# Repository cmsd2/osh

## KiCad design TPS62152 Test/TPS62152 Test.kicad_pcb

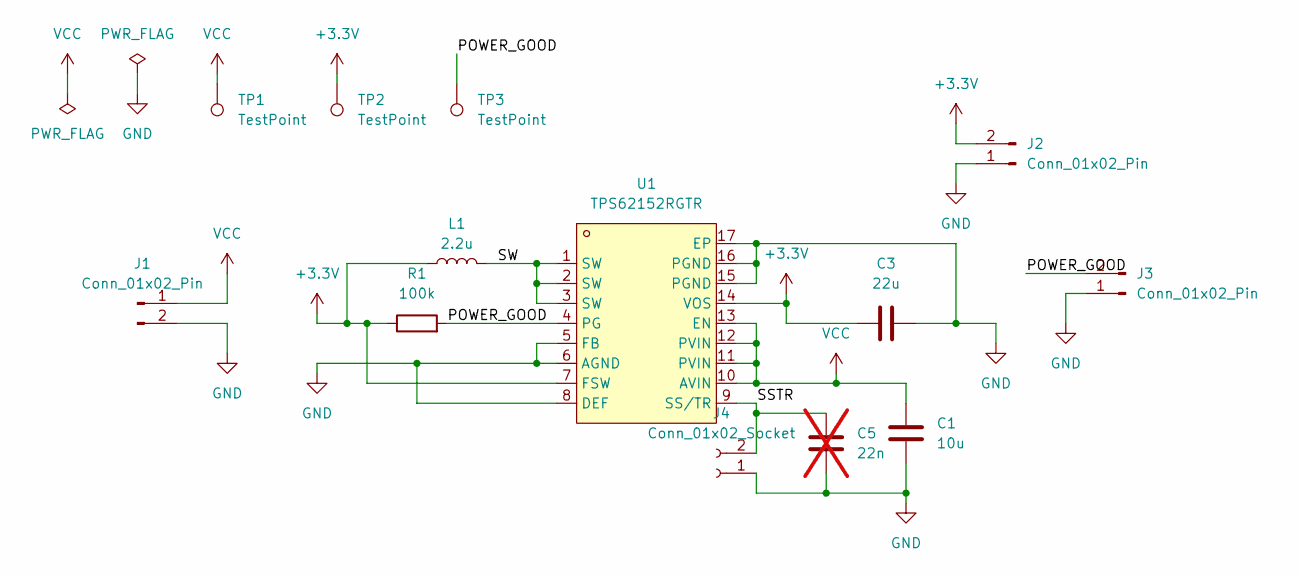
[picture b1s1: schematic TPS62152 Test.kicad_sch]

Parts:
C1: 10u; C0805; LCSC C440198
C3: 22u; C0805; LCSC C440198
C5: 22n; C0603; LCSC C21122; not fitted
J1, J2, J3: Conn_01x02_Pin; HDR-TH_2P-P2.54-V-M
J4: Conn_01x02_Socket; PinSocket_1x02_P2.54mm_Vertical; LCSC C3322502
L1: 2.2u; IND-SMD_L2.5-W2.0-B; LCSC C22471111
R1: 100k; R0603; LCSC C14675
TP1, TP2, TP3: TestPoint; TestPoint_THTPad_1.0x1.0mm_Drill0.5mm
U1: TPS62152RGTR; TQFN-16_L3.0-W3.0-P0.50-TL-EP1.7; LCSC Part C2070611

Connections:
+3.3V: C3.1, J2.2, L1.1, R1.1, TP2.1, U1.7 (FSW), U1.14 (VOS)
/POWER_GOOD: J3.2, R1.2, TP3.1, U1.4 (PG)
/SSTR: C5.1, J4.2, U1.9 (SS/TR)
/SW: L1.2, U1.1 (SW), U1.2 (SW), U1.3 (SW)
GND: C1.2, C3.2, C5.2, J1.2, J2.1, J3.1, J4.1, U1.5 (FB), U1.6 (AGND), U1.8 (DEF), U1.15 (PGND), U1.16 (PGND), U1.17 (EP)
VCC: C1.1, J1.1, TP1.1, U1.10 (AVIN), U1.11 (PVIN), U1.12 (PVIN), U1.13 (EN)

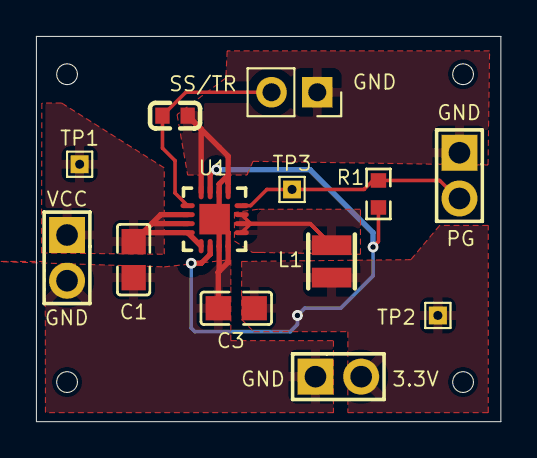
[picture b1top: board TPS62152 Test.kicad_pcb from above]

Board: 2 copper layers, 25.8 x 21.4 mm, 13 parts (0 on the bottom side), 6 nets.

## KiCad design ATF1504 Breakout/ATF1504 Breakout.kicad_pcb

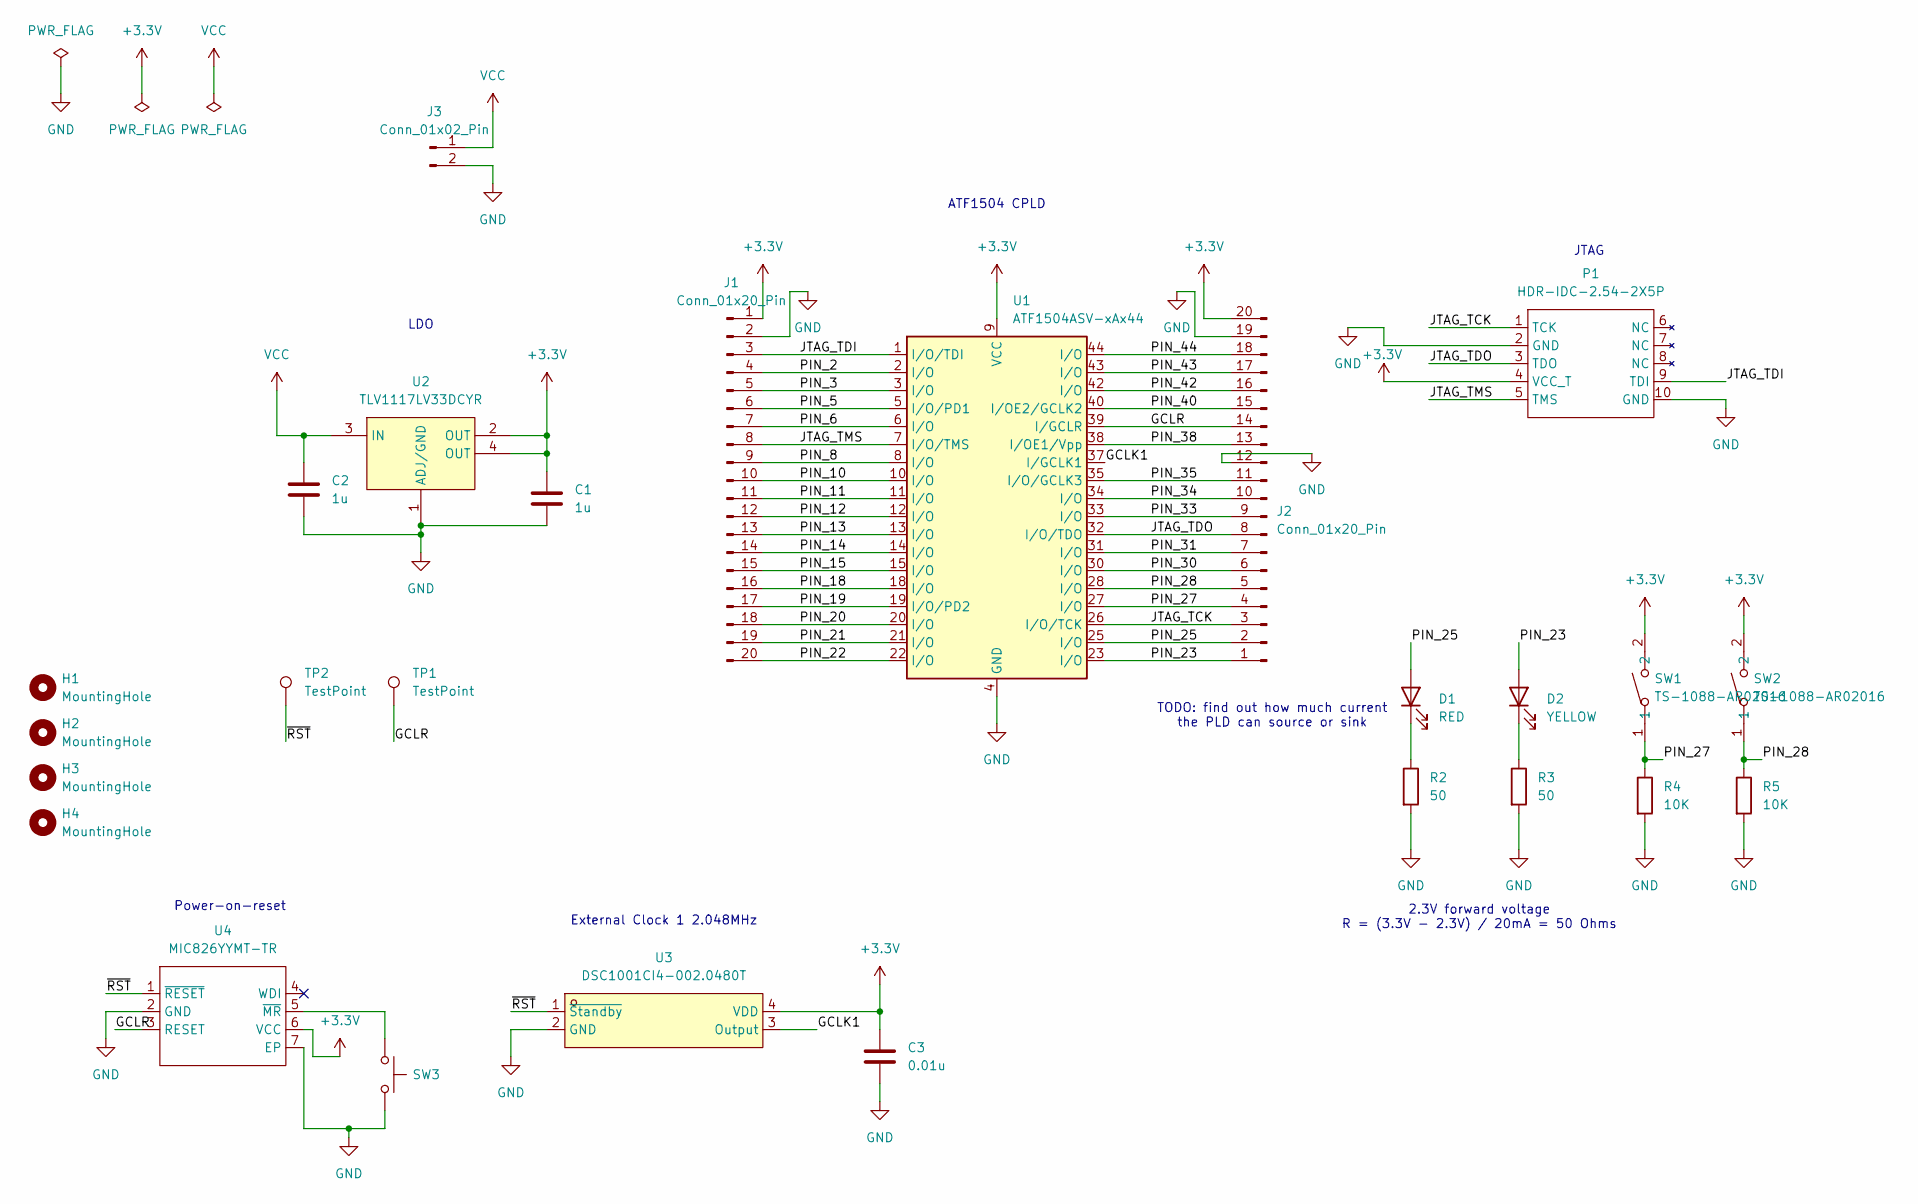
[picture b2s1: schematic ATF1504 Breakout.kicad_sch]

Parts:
C1, C2: 1u; C0603; LCSC C48579283
C3: 0.01u; C0603; LCSC C327204
D1: RED; LED0603-RD_RED; LCSC C965799
D2: YELLOW; LED0603-RD-YELLOW; LCSC C965803
H1, H2, H3, H4: MountingHole; MountingHole_3mm
J1, J2: Conn_01x20_Pin; HDR-TH_20P-P2.54-V-M-4; LCSC C7501591
J3: Conn_01x02_Pin; HDR-TH_2P-P2.54-V-M; LCSC C492401
P1: HDR-IDC-2.54-2X5P; IDC-TH_10P-P2.54_C5665; LCSC C5665
R2, R3: 50; R0603; LCSC C849792
R4, R5: 10K; R0603
SW1, SW2, SW3: TS-1088-AR02016; SW-SMD_L3.9-W3.0-P4.45; LCSC Part C720477
TP1, TP2: TestPoint; TestPoint_THTPad_1.0x1.0mm_Drill0.5mm
U1: ATF1504ASV-xAx44; TQFP-44_10x10mm_P0.8mm
U2: TLV1117LV33DCYR; SOT-223_L6.7-W3.5-P2.30-BR; LCSC Part C15578
U3: DSC1001CI4-002.0480T; OSC-SMD_4P-L3.2-W2.5-BL_1C210000BB0F; LCSC Part C611680
U4: MIC826YYMT-TR; TDFN-6_L2.0-W2.0-P0.65-TL-EP; LCSC Part C622518

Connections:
+3.3V: C1.1, C3.1, J1.1, J2.20, P1.4 (VCC_T), SW1.2, SW2.2, U1.9 (VCC), U1.17 (VCC), U1.29 (VCC), U1.41 (VCC), U2.2 (OUT), U2.4 (OUT), U3.4 (VDD), U4.6 (VCC)
/GCLK1: U1.37 (I/GCLK1), U3.3 (Output)
/GCLR: J2.14, TP1.1, U1.39 (I/GCLR), U4.3 (RESET)
/JTAG_TCK: J2.3, P1.1 (TCK), U1.26 (I/O/TCK)
/JTAG_TDI: J1.3, P1.9 (TDI), U1.1 (I/O/TDI)
/JTAG_TDO: J2.8, P1.3 (TDO), U1.32 (I/O/TDO)
/JTAG_TMS: J1.8, P1.5 (TMS), U1.7 (I/O/TMS)
/PIN_2: J1.4, U1.2 (I/O)
/PIN_3: J1.5, U1.3 (I/O)
/PIN_5: J1.6, U1.5 (I/O/PD1)
/PIN_6: J1.7, U1.6 (I/O)
/PIN_8: J1.9, U1.8 (I/O)
/PIN_10: J1.10, U1.10 (I/O)
/PIN_11: J1.11, U1.11 (I/O)
/PIN_12: J1.12, U1.12 (I/O)
/PIN_13: J1.13, U1.13 (I/O)
/PIN_14: J1.14, U1.14 (I/O)
/PIN_15: J1.15, U1.15 (I/O)
/PIN_18: J1.16, U1.18 (I/O)
/PIN_19: J1.17, U1.19 (I/O/PD2)
/PIN_20: J1.18, U1.20 (I/O)
/PIN_21: J1.19, U1.21 (I/O)
/PIN_22: J1.20, U1.22 (I/O)
/PIN_23: D2.2 (A), J2.1, U1.23 (I/O)
/PIN_25: D1.2 (A), J2.2, U1.25 (I/O)
/PIN_27: J2.4, R4.1, SW1.1, U1.27 (I/O)
/PIN_28: J2.5, R5.1, SW2.1, U1.28 (I/O)
/PIN_30: J2.6, U1.30 (I/O)
/PIN_31: J2.7, U1.31 (I/O)
/PIN_33: J2.9, U1.33 (I/O)
/PIN_34: J2.10, U1.34 (I/O)
/PIN_35: J2.11, U1.35 (I/O/GCLK3)
/PIN_38: J2.13, U1.38 (I/OE1/Vpp)
/PIN_40: J2.15, U1.40 (I/OE2/GCLK2)
/PIN_42: J2.16, U1.42 (I/O)
/PIN_43: J2.17, U1.43 (I/O)
/PIN_44: J2.18, U1.44 (I/O)
/~RST: TP2.1, U3.1 (~Standby), U4.1 (~RESET)
GND: C1.2, C2.2, C3.2, J1.2, J2.12, J2.19, J3.2, P1.2 (GND), P1.10 (GND), R2.2, R3.2, R4.2, R5.2, SW3.2, U1.4 (GND), U1.16 (GND), U1.24 (GND), U1.36 (GND), U2.1 (ADJ/GND), U3.2 (GND), U4.2 (GND), U4.7 (EP)
unnamed: D1.1 (K), R2.1
unnamed: D2.1 (K), R3.1
unnamed: SW3.1, U4.5 (~MR)
VCC: C2.1, J3.1, U2.3 (IN)

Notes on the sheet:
Power-on-reset
2.3V forward voltage R = (3.3V - 2.3V) / 20mA = 50 Ohms
ATF1504 CPLD
TODO: find out how much current the PLD can source or sink
External Clock 1 2.048MHz
JTAG
LDO

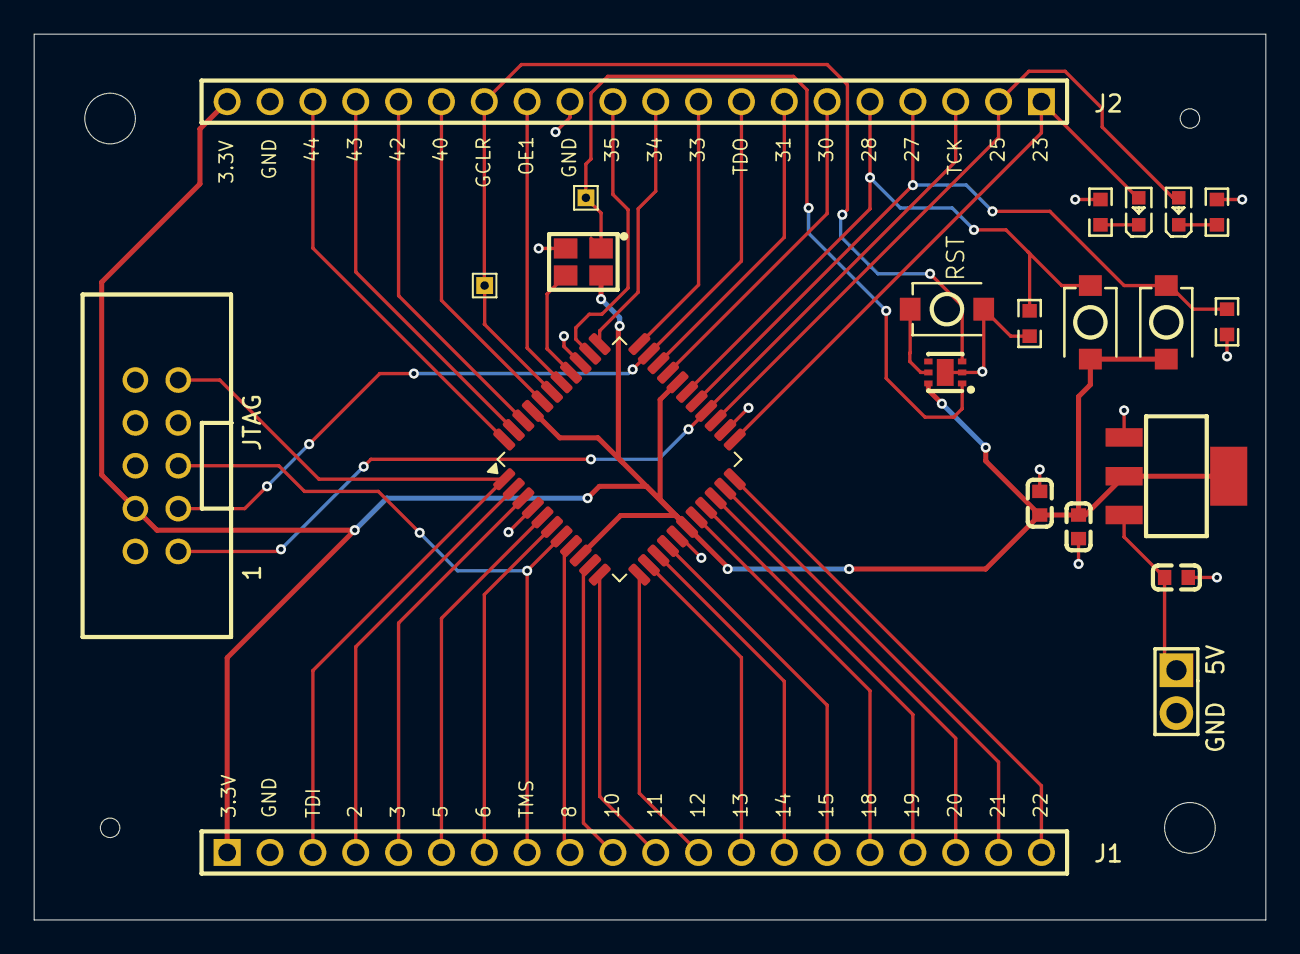
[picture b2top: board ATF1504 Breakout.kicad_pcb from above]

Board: 2 copper layers, 73.0 x 52.5 mm, 26 parts (0 on the bottom side), 43 nets.

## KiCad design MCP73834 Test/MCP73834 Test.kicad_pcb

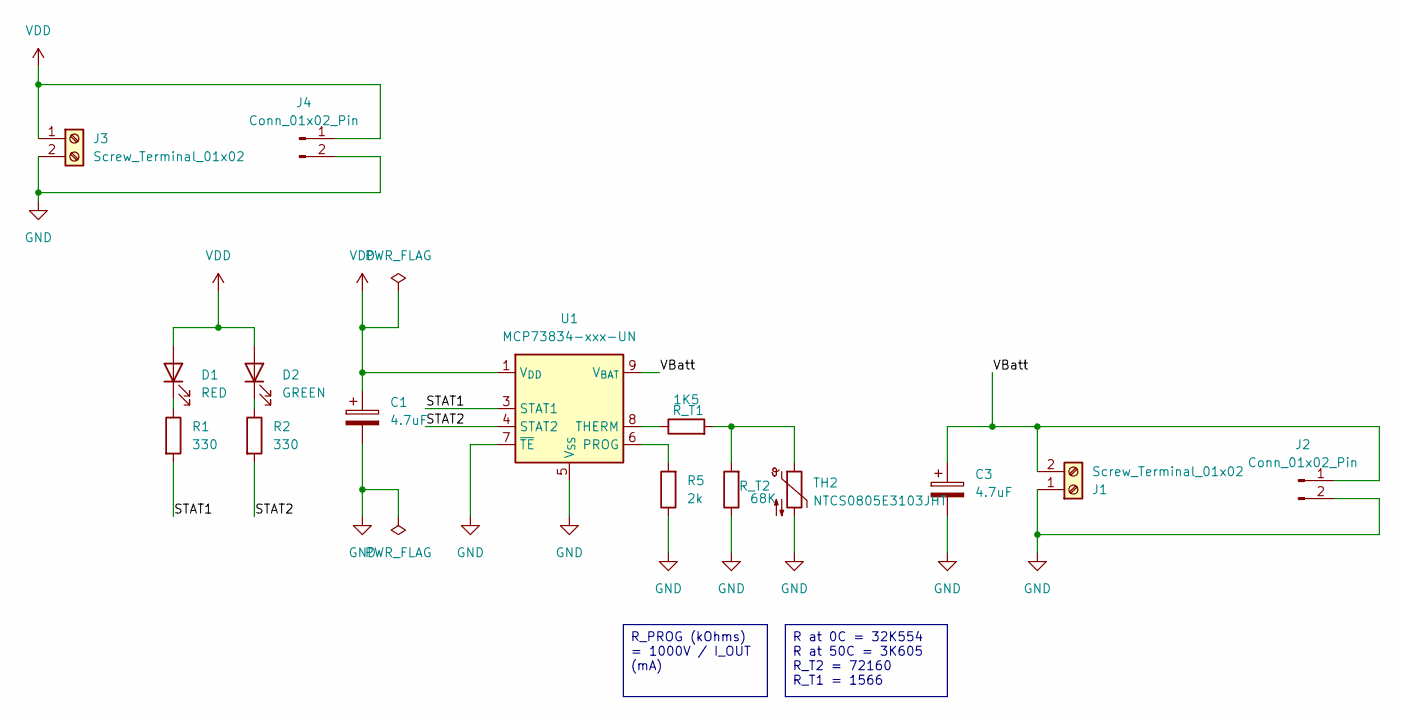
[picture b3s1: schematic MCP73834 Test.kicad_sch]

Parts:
C1, C3: 4.7uF; CAP-SMD_BD4.0-L4.3-W4.3-FD; LCSC C41435083
D1: RED; LED0805-RD_RED; LCSC C965812
D2: GREEN; LED0805-RD_GREEN; LCSC C965815
J1, J3: Screw_Terminal_01x02; CONN-TH_XY308-2.54-2P; LCSC C557685
J2, J4: Conn_01x02_Pin; HDR-TH_2P-P2.54-V-M; LCSC C7402729
R1, R2: 330; R0805; LCSC C105878
R3: 1K5; R0805; LCSC C114555
R4: 68K; R0805; LCSC C865614
R5: 2k; R0805; LCSC C114748
TH2: NTCS0805E3103JHT; R0805; LCSC C511025
U1: MCP73834-xxx-UN; MSOP-10_3x3mm_P0.5mm

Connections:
/STAT1: R1.2, U1.3 (STAT1)
/STAT2: R2.2, U1.4 (STAT2)
/VBatt: C3.1, J1.2, J2.1, U1.9 (V_{BAT}), U1.10 (V_{BAT})
GND: C1.2, C3.2, J1.1, J2.2, J3.2, J4.2, R4.1, R5.1, TH2.2, U1.5 (V_{SS}), U1.7 (~TE)
unnamed: D1.1 (K), R1.1
unnamed: D2.1 (K), R2.1
unnamed: R3.2, R4.2, TH2.1
unnamed: R5.2, U1.6 (PROG)
unnamed: R3.1, U1.8 (THERM)
VDD: C1.1, D1.2 (A), D2.2 (A), J3.1, J4.1, U1.1 (V_{DD}), U1.2 (V_{DD})

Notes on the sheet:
R_PROG (kOhms) = 1000V / I_OUT (mA)
R at 0C = 32K554 R at 50C = 3K605 R_T2 = 72160 R_T1 = 1566

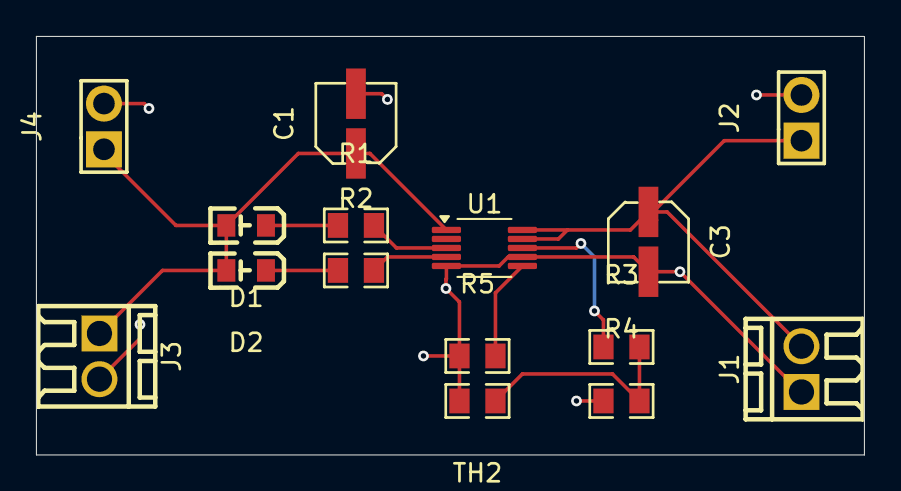
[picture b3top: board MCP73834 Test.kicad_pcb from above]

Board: 2 copper layers, 46.0 x 23.2 mm, 15 parts (0 on the bottom side), 10 nets.

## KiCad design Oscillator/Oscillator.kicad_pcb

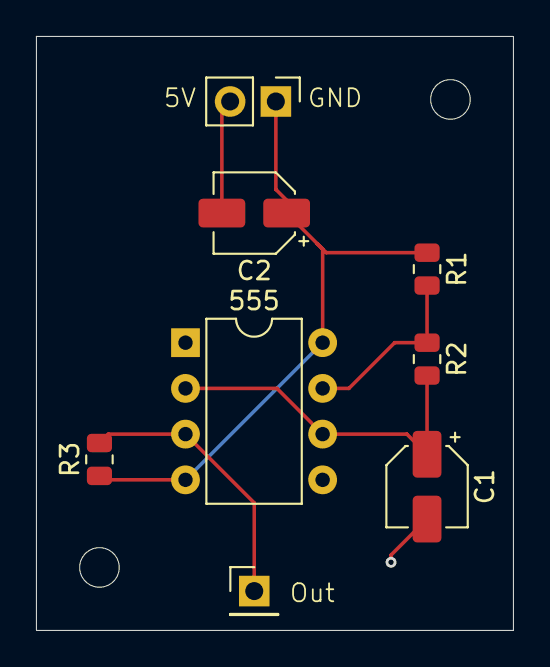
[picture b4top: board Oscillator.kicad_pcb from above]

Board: 2 copper layers, 26.5 x 33.0 mm, 8 parts (0 on the bottom side), 5 nets.

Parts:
555: NE555P; DIP-8_W7.62mm
C1, C2: C_Polarized; CP_Elec_4x5.4
J1: Conn_01x01_Pin; PinHeader_1x01_P2.54mm_Vertical
J2: Conn_01x02_Pin; PinHeader_1x02_P2.54mm_Vertical
R1, R2, R3: R; R_0805_2012Metric

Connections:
/Output: 555.3 (Q), J1.1, R3.2
/Trigger: 555.2 (TR), 555.6 (THR), C1.1, R2.2
GND: 555.1 (GND), C1.2, C2.2, J2.2
unnamed: 555.7 (DIS), R1.2, R2.1
VCC 5V: 555.4 (R), 555.8 (VCC), C2.1, J2.1, R1.1, R3.1

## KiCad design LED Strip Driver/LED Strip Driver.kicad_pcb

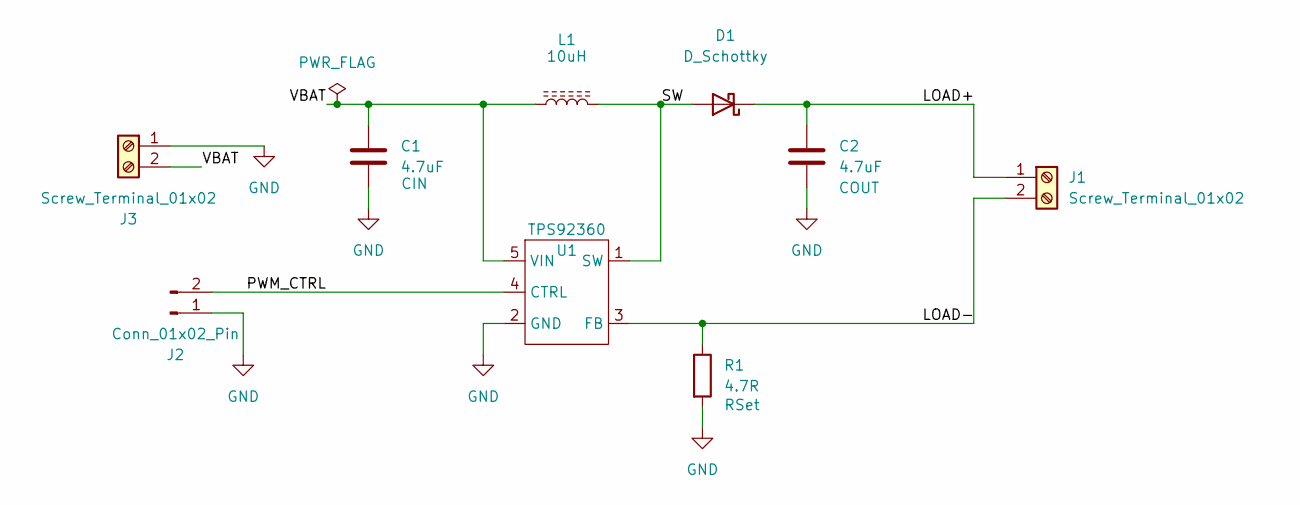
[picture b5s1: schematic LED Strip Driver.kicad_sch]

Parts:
C1, C2: 4.7uF; C_0805_2012Metric_Pad1.18x1.45mm_HandSolder; Part CL21A475KBQNNNE
D1: D_Schottky; D_SOD-323_HandSoldering; Part NSR0240HT1G
J1, J3: Screw_Terminal_01x02; TerminalBlock_Phoenix_PT-1,5-2-5.0-H_1x02_P5.00mm_Horizontal
J2: Conn_01x02_Pin; PinHeader_1x02_P2.54mm_Vertical
L1: 10uH; L_Coilcraft_LPS4018; Part LPS4018-103MRC
R1: 4.7R; R_0805_2012Metric_Pad1.20x1.40mm_HandSolder; Part CRCW08054R70FNEA
U1: TPS92360; SOT65P210X110-5N

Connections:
/LOAD+: C2.1, D1.1 (K), J1.1
/LOAD-: J1.2, R1.1, U1.3 (FB)
/PWM_CTRL: J2.2, U1.4 (CTRL)
/SW: D1.2 (A), L1.2, U1.1 (SW)
/VBAT: C1.1, J3.2, L1.1, U1.5 (VIN)
GND: C1.2, C2.2, J2.1, J3.1, R1.2, U1.2 (GND)

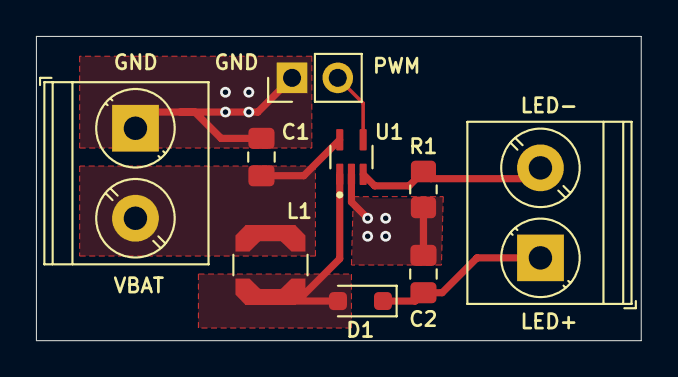
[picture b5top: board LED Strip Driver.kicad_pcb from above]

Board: 2 copper layers, 33.6 x 16.9 mm, 9 parts (0 on the bottom side), 6 nets.

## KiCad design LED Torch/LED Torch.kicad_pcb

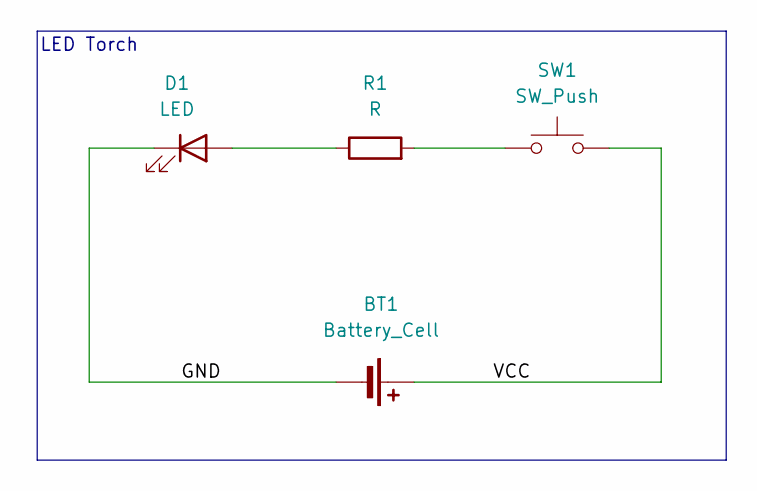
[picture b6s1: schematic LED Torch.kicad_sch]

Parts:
BT1: Battery_Cell; BatteryHolder_Keystone_1058_1x2032
D1: LED; LED_D5.0mm
R1: R; R_Axial_DIN0204_L3.6mm_D1.6mm_P7.62mm_Horizontal
SW1: SW_Push; SW_TH_Tactile_Omron_B3F-10xx

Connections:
/GND: BT1.2 (-), D1.1 (K)
/VCC: BT1.1 (+), SW1.2
unnamed: D1.2 (A), R1.1
unnamed: R1.2, SW1.1

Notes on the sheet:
LED Torch

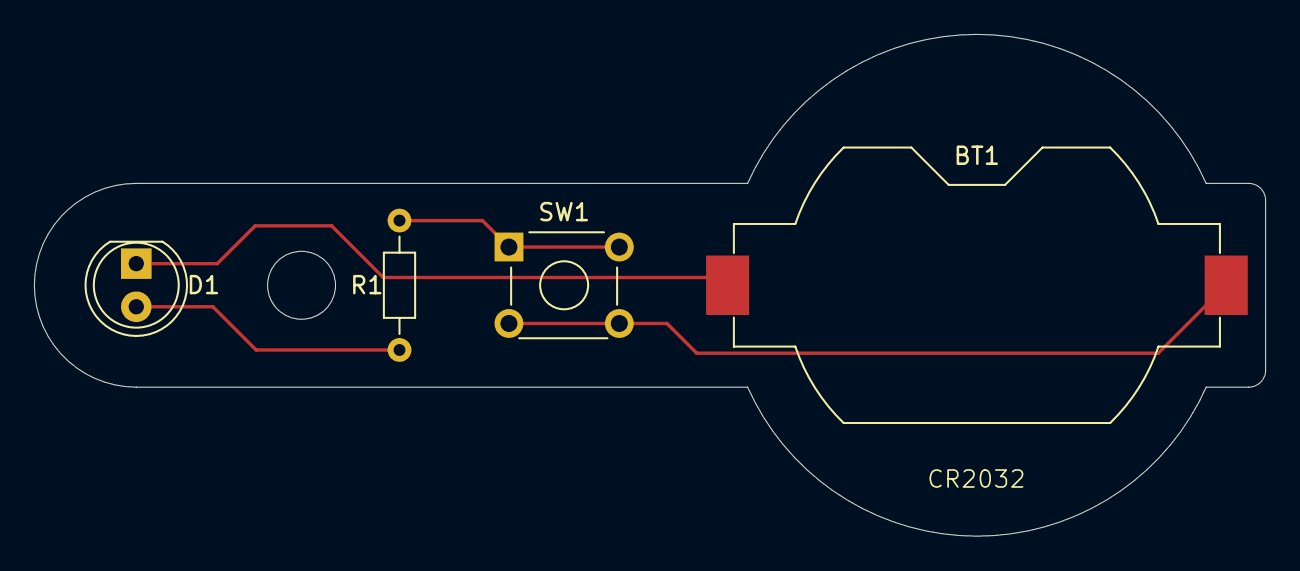
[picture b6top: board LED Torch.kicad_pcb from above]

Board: 2 copper layers, 72.5 x 29.5 mm, 4 parts (0 on the bottom side), 4 nets.

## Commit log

2015-04-22 basic blinkyboard from jeremy blum's eagle tutorial
2015-04-22 code from jeremy's tutorial is GPLv3
2015-05-13 lpc810 blinky
2015-05-13 reverse polarity protection using a p-channel mosfet
2015-05-13 add readme
2015-05-13 add link
2024-08-08 simple led torch schematic
2024-08-09 add components to pcb
2024-08-10 basic layout
2024-08-10 complete layout
2024-08-10 add battery charging circuit
2024-08-15 reference design for battery charger
2024-08-30 add led strip driver reference
2024-09-02 complete pcb for led driver
2024-09-02 flip pwm connector so gnd pad is square
2025-08-29 add buck boost test
2025-09-22 add 555 astable timer
2025-09-22 add spreadsheet for calculating resistor values
2025-10-02 add pcb design and lcsc part numbers
2025-10-07 add atf1504asv breakout board
2025-10-09 route tracks and add graphics
2025-10-10 add power-on-reset and switch and led peripherals
2025-10-11 replace two of the mounting holes with tooling holes for assembly
2025-10-16 add 3.3v buck power test circuit
2025-10-16 tidy up
2025-10-16 add graphics
2025-10-16 update part numbers
2025-10-16 ignore
